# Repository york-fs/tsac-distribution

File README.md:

# TSAC Distribution Board

The TSAC distribution board is the interface between the PCBs inside the TSAC and the rest of the LVS. It connects to
the rear distribution via a 23-pin AMPSEAL connector and connects primarily to the BMS, IMD, and precharge PCB inside of
the TSAC. It also provides split termination for the CAN bus.

[Latest Release](https://github.com/york-fs/tsac-distribution/releases/latest)
[Interactive BOM](https://york-fs.github.io/tsac-distribution/ibom.html)

## Cloning

A recursive clone must be used to download the `kicad-library` repository:

    git clone --recursive https://github.com/york-fs/tsac-distribution.git

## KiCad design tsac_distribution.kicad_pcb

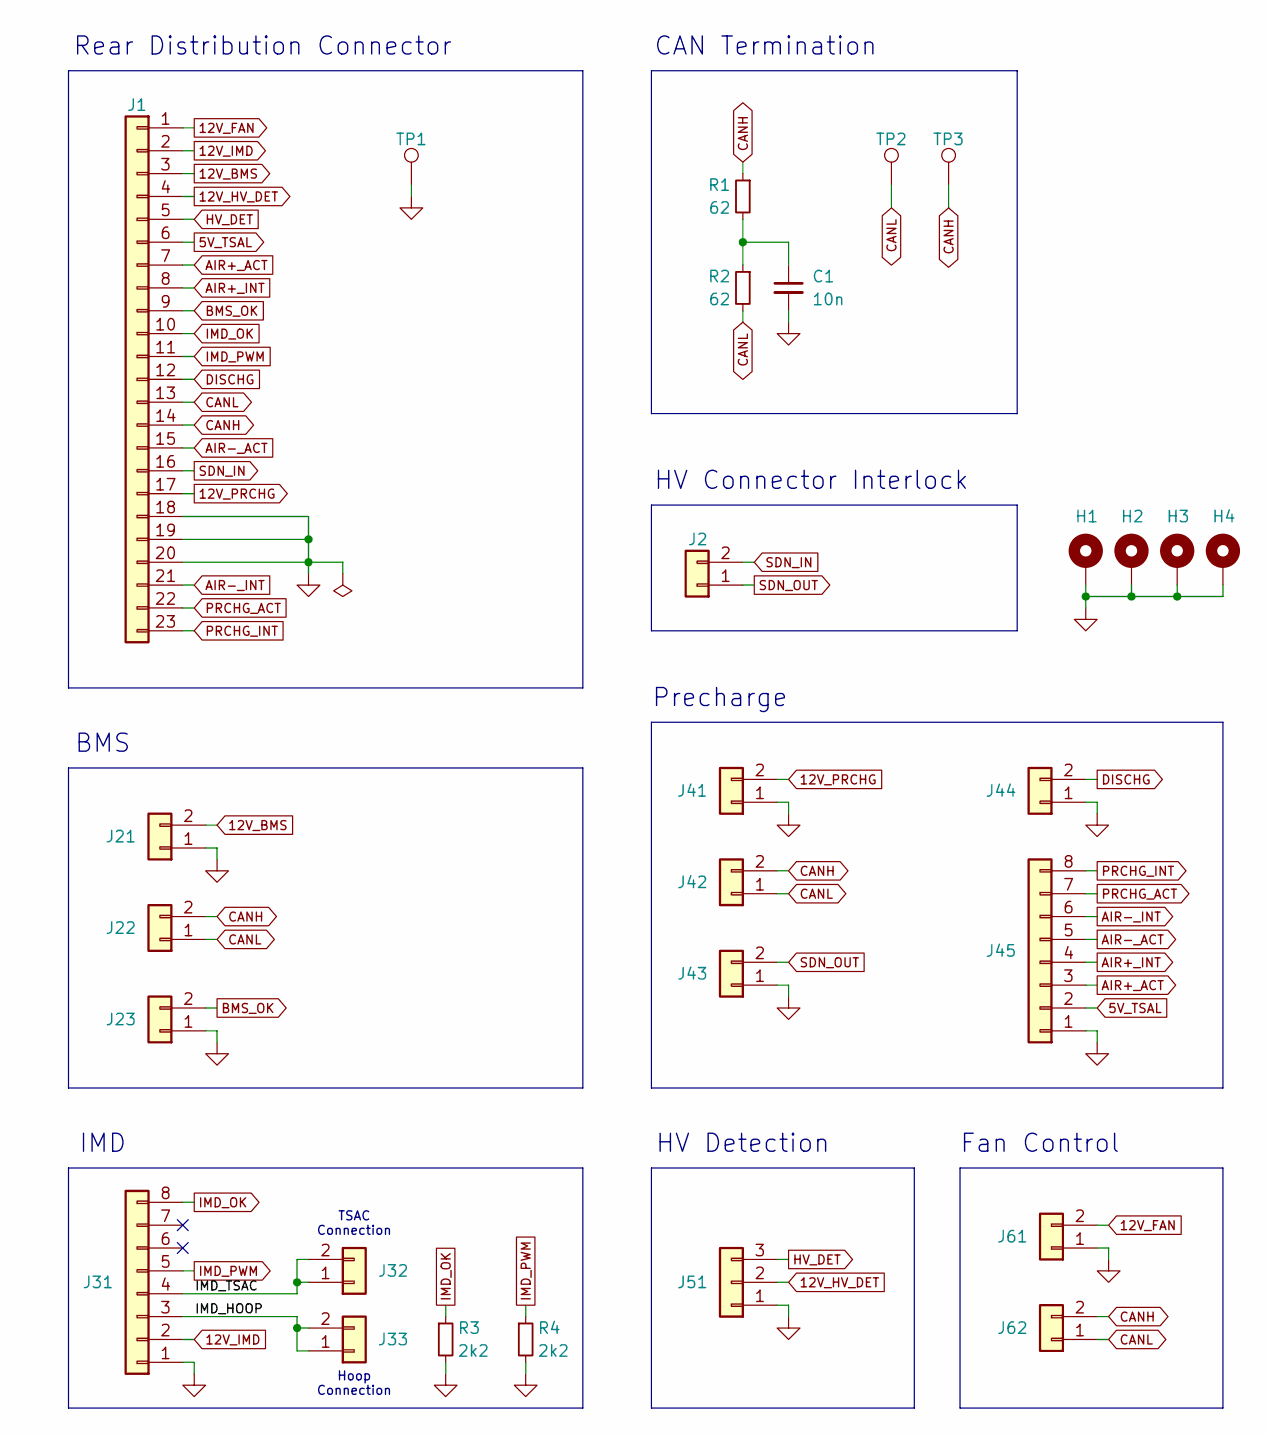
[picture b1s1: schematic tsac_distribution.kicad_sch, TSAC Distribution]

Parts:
C1: 10n; C_0603_1608Metric
H1, H2, H3, H4: MountingHole_Pad; MountingHole_3.2mm_M3_Pad_Via
J1: Conn_01x23; AMPSEAL-23-776087; Mfr # 776087-1; DigiKey # A107007-ND
J2, J43, J44: Conn_01x02; MolexMicrofitPlus1x2; Mfr # 2157601032; DigiKey # 900-2157601032-ND
J21, J41, J61: Conn_01x02; MolexMicrofitPlus1x2; Mfr # 2157601022; DigiKey # 900-2157601022-ND
J22, J23, J32, J33, J42, J62: Conn_01x02; MolexMicrofitPlus1x2; Mfr # 2157601002; DigiKey # 900-2157601002-ND
J31: Conn_01x08; MolexMicrofitPlus1x8; Mfr # 2-1445088-8; DigiKey # 2-1445088-8-ND
J45: Conn_01x08; MolexMicrofitPlus1x8; Mfr # 2157601008; DigiKey # 900-2157601008-ND
J51: Conn_01x03; MolexMicrofitPlus1x3; Mfr # 2157601003; DigiKey # 900-2157601003-ND
R1, R2: 62; R_1206_3216Metric; Mfr # CRCW120662R0JNEAHP; DigiKey # 541-62UACT-ND
R3, R4: 2k2; R_0603_1608Metric
TP1: TestPoint; TestPoint_Keystone_5019_Miniature; Mfr # 5019; DigiKey # 36-5019CT-ND
TP2, TP3: TestPoint; TestPoint_Keystone_5000-5004_Miniature

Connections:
5V_TSAL: J1.6, J45.2
12V_BMS: J1.3, J21.2
12V_FAN: J1.1, J61.2
12V_HV_DET: J1.4, J51.2
12V_IMD: J1.2, J31.2
12V_PRCHG: J1.17, J41.2
/IMD_HOOP: J31.3, J33.1, J33.2
/IMD_TSAC: J31.4, J32.1, J32.2
AIR+_ACT: J1.7, J45.3
AIR+_INT: J1.8, J45.4
AIR-_ACT: J1.15, J45.5
AIR-_INT: J1.21, J45.6
BMS_OK: J1.9, J23.2
CANH: J1.14, J22.2, J42.2, J62.2, R1.1, TP3.1
CANL: J1.13, J22.1, J42.1, J62.1, R2.2, TP2.1
DISCHG: J1.12, J44.2
GND: C1.2, H1.1, H2.1, H3.1, H4.1, J1.18, J1.19, J1.20, J21.1, J23.1, J31.1, J41.1, J43.1, J44.1, J45.1, J51.1, J61.1, R3.2, R4.2, TP1.1
HV_DET: J1.5, J51.3
IMD_OK: J1.10, J31.8, R3.1
IMD_PWM: J1.11, J31.5, R4.1
unnamed: C1.1, R1.2, R2.1
PRCHG_ACT: J1.22, J45.7
PRCHG_INT: J1.23, J45.8
SDN_IN: J1.16, J2.2
SDN_OUT: J2.1, J43.2

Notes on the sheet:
HV Connector Interlock
CAN Termination
Rear Distribution Connector
HV Detection
Fan Control
Precharge
BMS
Hoop Connection
IMD
TSAC Connection

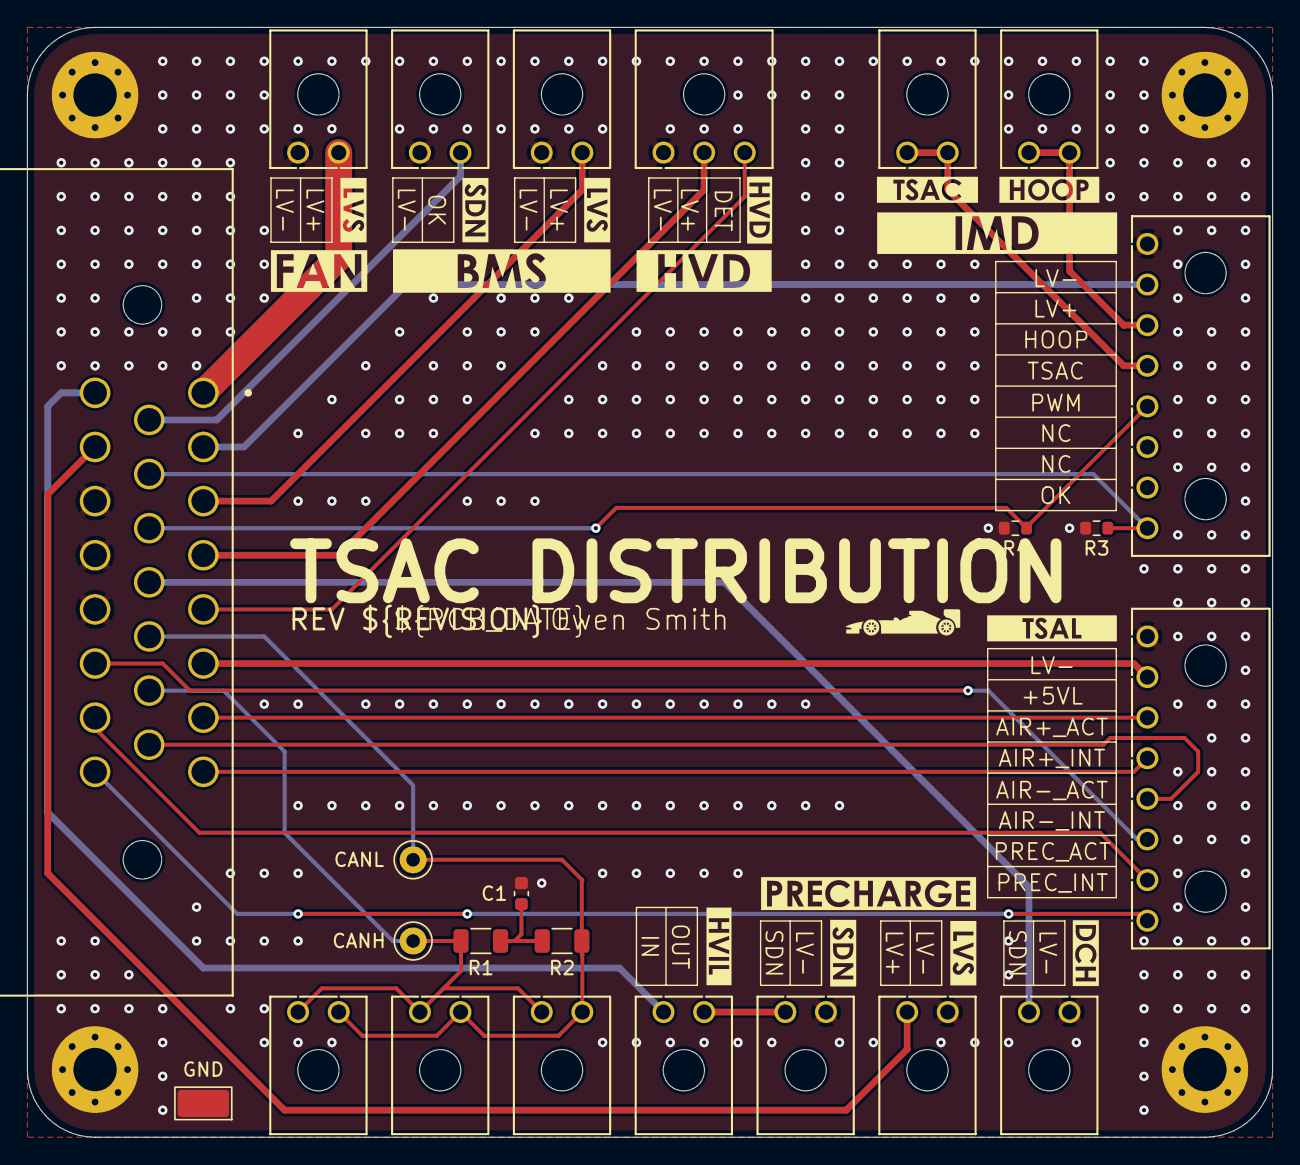
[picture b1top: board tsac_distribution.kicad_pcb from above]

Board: 2 copper layers, 92.0 x 82.0 mm, 44 parts (0 on the bottom side), 25 nets.

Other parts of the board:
kibuzzard-6A07B746: G***; kibuzzard-6A07B746
kibuzzard-6A07B875: G***; kibuzzard-6A07B875
kibuzzard-6A07C1EF: G***; kibuzzard-6A07C1EF
kibuzzard-6A3540DA: G***; kibuzzard-6A3540DA
kibuzzard-6A3541C8: G***; kibuzzard-6A3541C8
kibuzzard-6A35413C: G***; kibuzzard-6A35413C
kibuzzard-6A35415C: G***; kibuzzard-6A35415C
kibuzzard-6A088056: G***; kibuzzard-6A088056
kibuzzard-6A354048: G***; kibuzzard-6A354048
kibuzzard-6A354054: G***; kibuzzard-6A354054
kibuzzard-6A354262: G***; kibuzzard-6A354262
kibuzzard-6A354707: G***; kibuzzard-6A354707
kibuzzard-6910B7D7, kibuzzard-6910B7D7#2, kibuzzard-6910B7D7#3: G***; kibuzzard-6910B7D7
kibuzzard-6940937D: G***; kibuzzard-6940937D

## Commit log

2026-06-19 *: Add layout
2026-06-19 pcb: Run track cleanup
2026-06-23 pcb: Setup AISLER push
2026-06-26 ci: Add KiCad CI
2026-06-26 meta: Add README
2026-06-26 pcb: Add models for Molex MF+ 1x8 connectors
